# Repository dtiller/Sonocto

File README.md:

# Sonocto

This repo contains the MPLAB PIC code, Kicad board definition, and Arduino library and test suite for the Sonocto(tm) eight channel sonar module controller.

The author(s) assume/s no liability for your use of this code and no warranty, express or implied, exists.

The latest version is in the SonoctoPlus directory and uses a '1525 PIC. The code in the non-Plus directory is written for a '1523 PIC and may not have all of the features of the Plus version.

See the main.h and main.c files for details of the I2C protocol.

There are examples and test cases in the arduino area.

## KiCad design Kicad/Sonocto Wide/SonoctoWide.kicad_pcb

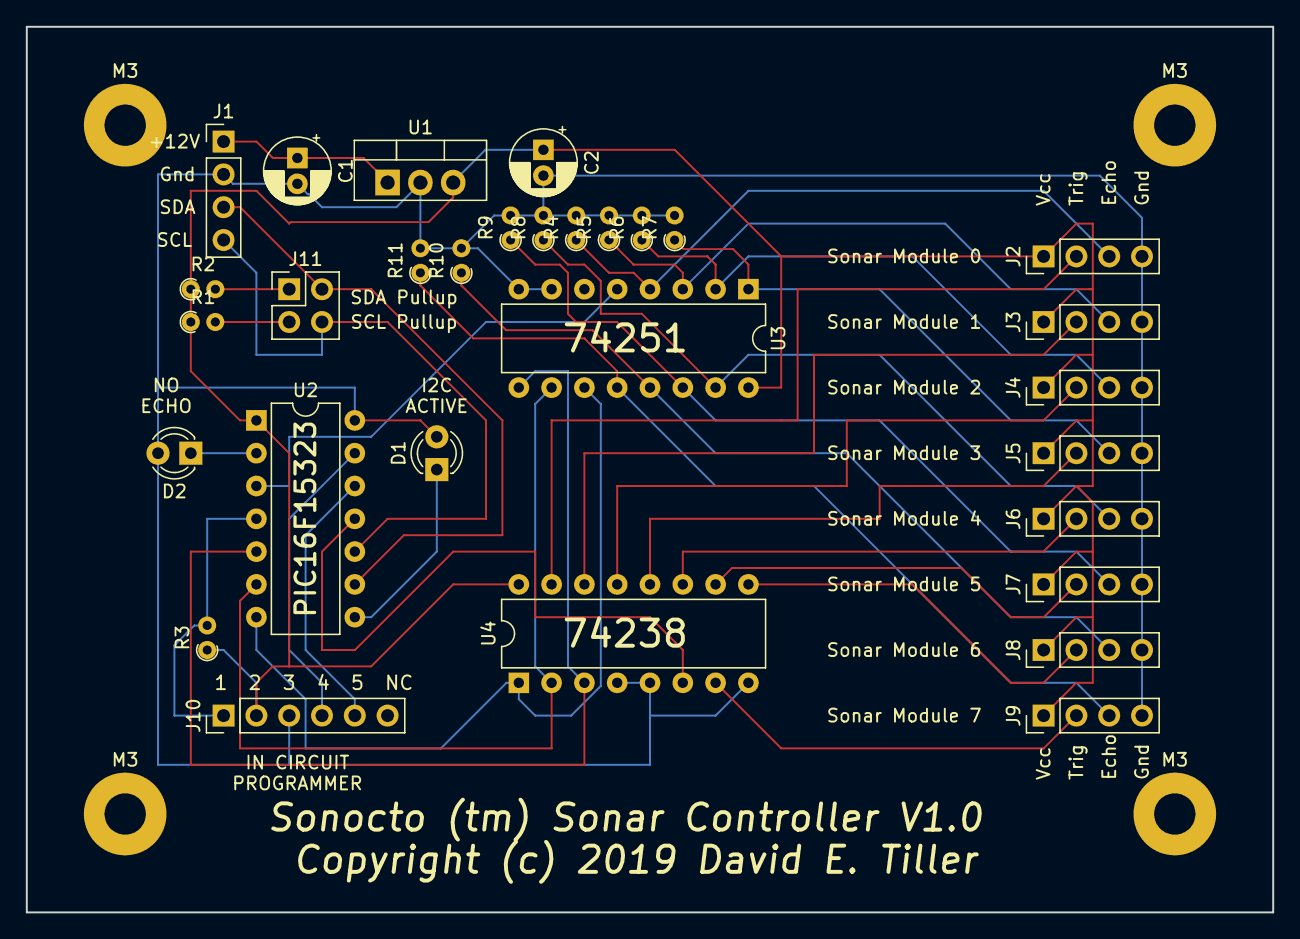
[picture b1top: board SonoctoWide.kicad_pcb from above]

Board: 2 copper layers, 96.5 x 68.6 mm, 34 parts (0 on the bottom side), 33 nets.

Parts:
C1, C2: 0.47 uF; CP_Radial_D5.0mm_P2.00mm
D1: YL_LED; LED_D3.0mm
D2: RD_LED; LED_D3.0mm
J1: Conn_01x04; PinHeader_1x04_P2.54mm_Vertical
J2: Sonar 0; PinHeader_1x04_P2.54mm_Vertical
J3: Sonar 1; PinHeader_1x04_P2.54mm_Vertical
J4: Sonar 2; PinHeader_1x04_P2.54mm_Vertical
J5: Sonar 3; PinHeader_1x04_P2.54mm_Vertical
J6: Sonar 4; PinHeader_1x04_P2.54mm_Vertical
J7: Sonar 5; PinHeader_1x04_P2.54mm_Vertical
J8: Sonar 6; PinHeader_1x04_P2.54mm_Vertical
J9: Sonar 7; PinHeader_1x04_P2.54mm_Vertical
J10: ICSP; PinHeader_1x06_P2.54mm_Vertical
J11: Conn_02x02_Odd_Even; PinHeader_2x02_P2.54mm_Vertical
M3, M3#2, M3#3, M3#4: MountingHole_3.2mm_M3_Pad
R1, R2: 4.7k; R_Axial_DIN0204_L3.6mm_D1.6mm_P1.90mm_Vertical
R3, R4, R5, R6, R7, R8, R9, R10, R11: 10k; R_Axial_DIN0204_L3.6mm_D1.6mm_P1.90mm_Vertical
U1: L7805; TO-220-3_Vertical
U2: PIC16F15323-IP; DIP-14_W7.62mm
U3: 74LS251; DIP-16_W7.62mm
U4: 74HC238; DIP-16_W7.62mm

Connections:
+5V: C2.1, J2.1, J3.1, J4.1, J5.1, J6.1, J7.1, J8.1, J9.1, J10.2, R1.1, R2.1, R3.1, U1.3, U2.1, U3.16, U4.16
+12V: C1.1, J1.1, U1.1
GND: C1.2, C2.2, D1.2, D2.2, J1.2, J2.4, J3.4, J4.4, J5.4, J6.4, J7.4, J8.4, J9.4, J10.3, R4.2, R5.2, R6.2, R7.2, R8.2, R9.2, R10.2, R11.2, U1.2, U2.14, U3.7, U3.8, U4.4, U4.5, U4.8
unnamed: D1.1, U2.8
unnamed: D2.1, U2.2
unnamed: J1.3, J11.2, U2.9
unnamed: J1.4, J11.4, U2.10
unnamed: J2.2, U4.15
unnamed: J2.3, R4.1, U3.4
unnamed: J3.2, U4.14
unnamed: J3.3, R5.1, U3.3
unnamed: J4.2, U4.13
unnamed: J4.3, R6.1, U3.2
unnamed: J5.2, U4.12
unnamed: J5.3, R7.1, U3.1
unnamed: J6.2, U4.11
unnamed: J6.3, R8.1, U3.15
unnamed: J7.2, U4.10
unnamed: J7.3, R9.1, U3.14
unnamed: J8.2, U4.9
unnamed: J8.3, R10.1, U3.13
unnamed: J9.2, U4.7
unnamed: J9.3, R11.1, U3.12
unnamed: J10.1, R3.2, U2.4
unnamed: J10.4, U2.13
unnamed: J10.5, U2.12
unnamed: J11.1, R2.2
unnamed: J11.3, R1.2
unnamed: U2.3, U3.5
unnamed: U2.5, U3.9, U4.3
unnamed: U2.6, U3.10, U4.2
unnamed: U2.7, U3.11, U4.1
unnamed: U2.11, U4.6

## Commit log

2019-04-14 Adding .gitignore and updated README.md
2019-04-14 Added remainder of files.
2019-04-20 Added reboot and setI2CAddr commands.
    Moved config management command.
    Changed config EPROM layout - added i2c addr in there.
    Added test for reboot.
    Added copyArduino.sh script to copy over the files since Arduino doesn't like projects and
    libraries anywhere but under it's 'home' folder.
    TODO:
2019-04-21 Added hole center-to-center dimension.
2019-04-22 1) Added change I2C address logic. The valid address range is UPPER_I2C_BITS to UPPER_I2C_BITS + 0x1F (0x20-0x3F). 2) Created new Arduino sketch to change I2C addresses on boards. 3) Added just-in-ca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
2019-04-24 Added CHANNEL #define to test suite. Changed programmer to low voltage (again).
2019-04-24 Added getDistanceMeters and getDistanceFeet.
2019-04-24 Added tests for feet and meters.
2019-04-25 1) Added getVersion command. 2) removed copy script - use symbolic links instead.
2019-04-25 1) Added getVersion 2) Deleted copy script - use symbolic links instead 3) changed double to float for getDistanceXXXX
2019-04-25 Added getVersion. Deleted script. Made distances floats.
2019-04-26 Added builds directory w/ version 1.0
2019-04-28 Added config area to ROM definition in the linker config.

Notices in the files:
Kicad/Sonocto Wide/SonoctoWide.kicad_pcb:
Copyright (c) 2019 David E. Tiller
